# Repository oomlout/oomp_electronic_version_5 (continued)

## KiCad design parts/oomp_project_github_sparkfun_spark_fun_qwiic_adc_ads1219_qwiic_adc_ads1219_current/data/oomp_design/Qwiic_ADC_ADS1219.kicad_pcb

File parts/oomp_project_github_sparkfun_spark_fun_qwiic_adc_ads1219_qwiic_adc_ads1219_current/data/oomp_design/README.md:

# OOMP KiCad design copy

Open `Qwiic_ADC_ADS1219.kicad_pro` (or the `.kicad_pcb` / `.kicad_sch`) in KiCad. Local OOMP libraries are under `libraries/`. Original inputs are preserved in [../original/](../original/).

Only verified unchanged installed KiCad defaults were renamed. Modified, custom, unmatched and unavailable items remain unchanged. Soldering variants are never swapped during conversion. Existing pad coordinates, nets and UUIDs are preserved.

See [conversion_report.yaml](conversion_report.yaml) for every conversion and skip. Copy this directory before editing; regeneration refuses to overwrite edited design files.

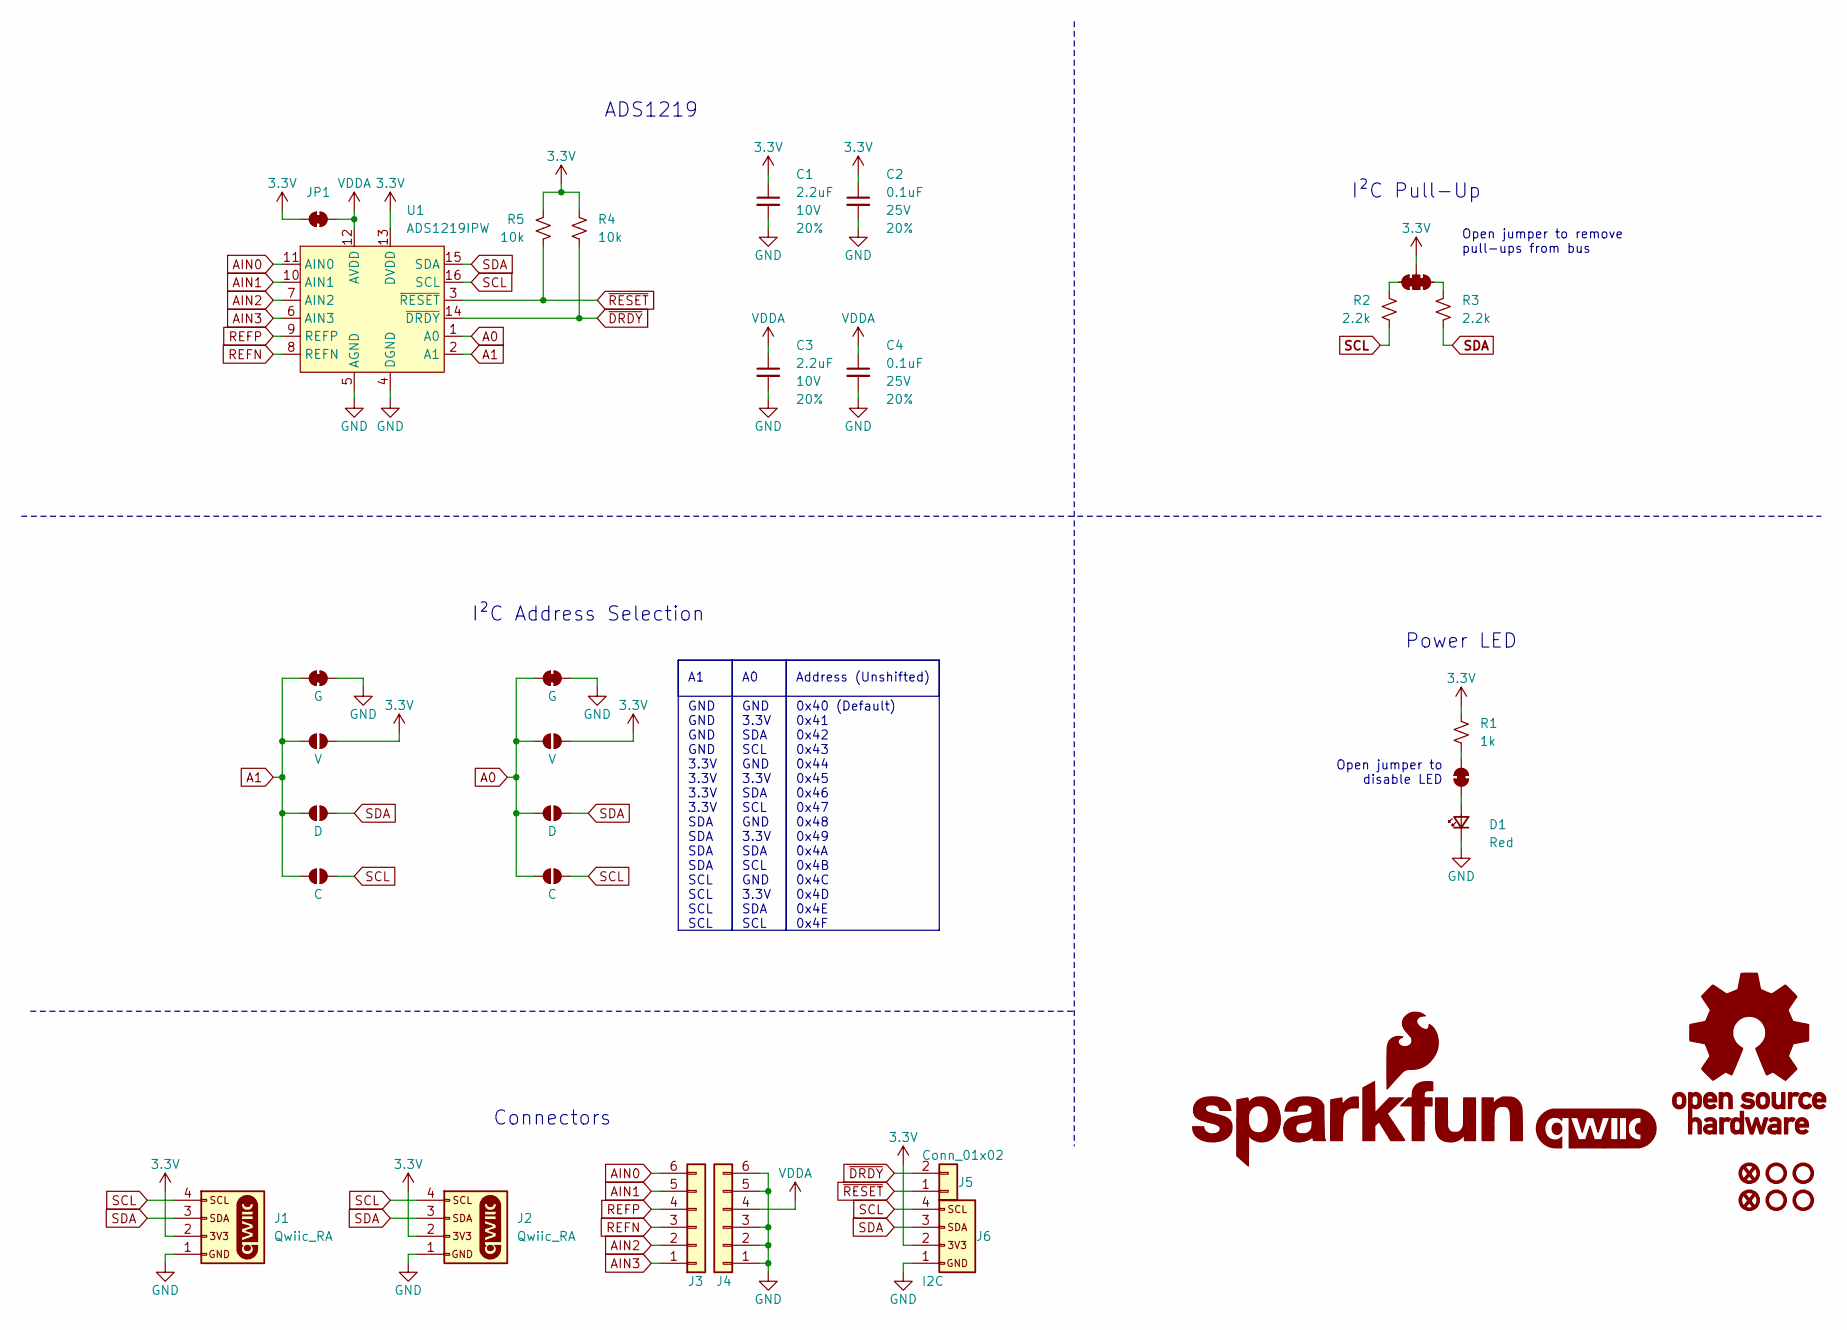
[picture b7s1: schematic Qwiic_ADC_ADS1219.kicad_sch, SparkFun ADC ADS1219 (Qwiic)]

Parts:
C1, C3: 2.2uF; C_0603_1608Metric; Voltage 10V; Tolerance 20%
C2, C4: 0.1uF; C_0603_1608Metric; Voltage 25V; Tolerance 20%
D1: Red; LED_0603_1608Metric_Red
FID1, FID3: Fiducial_0.5mm; Fiducial_0.5mm_Mask1mm
G1: SparkFun_Logo
J1, J2: Qwiic_RA; JST_SMD_1.0mm-4_Black
J3, J4: Conn_01x06; 1x06
J5: Conn_01x02; 1x02
J6: I2C; 1x04
JP1, JP2: Jumper_2_NC_Trace
JP3: Jumper_3_NC-2_Trace
JP4, JP8: G; Jumper_2_NC_Trace
JP5, JP9: V; Jumper_2_NO
JP6, JP10: D; Jumper_2_NO
JP7, JP11: C; Jumper_2_NO
R1: 1k; R_0603_1608Metric
R2, R3: 2.2k; R_0603_1608Metric
R4, R5: 10k; R_0603_1608Metric
ST1, ST2, ST3, ST4: Standoff
U1: ADS1219IPW; TSSOP-16

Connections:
3.3V: C1.1, C2.1, J1.2, J2.2, J6.2, JP1.1 (A), JP3.2 (B), JP5.2 (B), JP9.2 (B), R1.2, R4.2, R5.1, U1.13 (DVDD)
A0: JP4.1 (A), JP5.1 (A), JP6.1 (A), JP7.1 (A), U1.1 (A0)
A1: JP8.1 (A), JP9.1 (A), JP10.1 (A), JP11.1 (A), U1.2 (A1)
AIN0: J3.6, U1.11 (AIN0)
AIN1: J3.5, U1.10 (AIN1)
AIN2: J3.2, U1.7 (AIN2)
AIN3: J3.1, U1.6 (AIN3)
GND: C1.2, C2.2, C3.2, C4.2, D1.1 (K), J1.1, J2.1, J4.1, J4.2, J4.3, J4.5, J4.6, J6.1, JP4.2 (B), JP8.2 (B), U1.4 (DGND), U1.5 (AGND)
unnamed: D1.2 (A), JP2.1 (A)
unnamed: JP2.2 (B), R1.1
unnamed: JP3.1 (A), R3.1
unnamed: JP3.3 (C), R2.2
REFN: J3.3, U1.8 (REFN)
REFP: J3.4, U1.9 (REFP)
SCL: J1.4, J2.4, J6.4, JP7.2 (B), JP11.2 (B), R2.1, U1.16 (SCL)
SDA: J1.3, J2.3, J6.3, JP6.2 (B), JP10.2 (B), R3.2, U1.15 (SDA)
VDDA: C3.1, C4.1, J4.4, JP1.2 (B), U1.12 (AVDD)
~DRDY: J5.2, R4.1, U1.14 (~DRDY)
~RESET: J5.1, R5.2, U1.3 (~RESET)

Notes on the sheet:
Open jumper to remove pull-ups from bus
Connectors
Power LED
I²C Address Selection
Open jumper to disable LED
A1 GND GND GND GND 3.3V 3.3V 3.3V 3.3V SDA SDA SDA SDA SCL SCL SCL SCL
Address (Unshifted) 0x40 (Default) 0x41 0x42 0x43 0x44 0x45 0x46 0x47 0x48 0x49 0x4A 0x4B 0x4C 0x4D 0x4E 0x4F
ADS1219
I²C Pull-Up
A0 GND 3.3V SDA SCL GND 3.3V SDA SCL GND 3.3V SDA SCL GND 3.3V SDA SCL

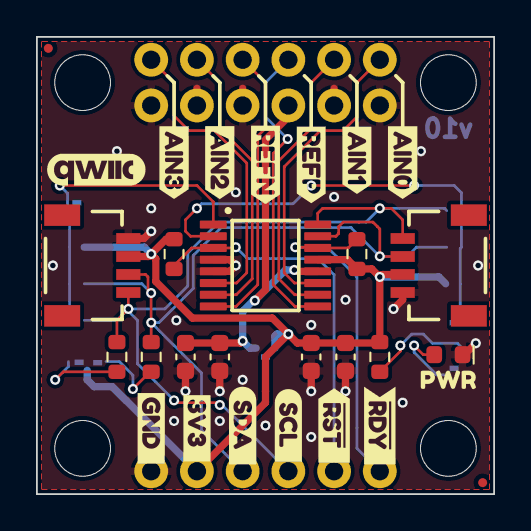
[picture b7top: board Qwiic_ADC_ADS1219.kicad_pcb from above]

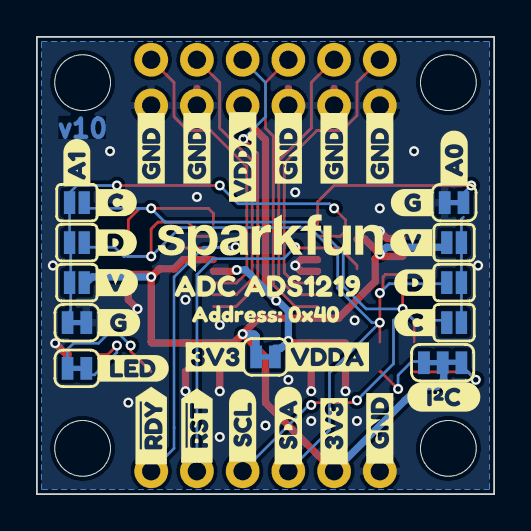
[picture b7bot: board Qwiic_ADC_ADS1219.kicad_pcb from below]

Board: 2 copper layers, 25.4 x 25.4 mm, 75 parts (39 on the bottom side), 19 nets.

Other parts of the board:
kibuzzard-64C3B30F: G***; kibuzzard-64C3B30F
kibuzzard-64C3BD7A: G***; kibuzzard-64C3BD7A
kibuzzard-64C36D1A: G***; kibuzzard-64C36D1A
kibuzzard-64C36D2D: G***; kibuzzard-64C36D2D
kibuzzard-64C36D5B: G***; kibuzzard-64C36D5B
kibuzzard-64C36D6C: G***; kibuzzard-64C36D6C
kibuzzard-64C36D47: G***; kibuzzard-64C36D47
kibuzzard-64C36D91: G***; kibuzzard-64C36D91
kibuzzard-64C37A88: G***; kibuzzard-64C37A88
kibuzzard-64C37CC9: G***; kibuzzard-64C37CC9
kibuzzard-64C38090: G***; kibuzzard-64C38090
kibuzzard-67BCC03F: G***; kibuzzard-67BCC03F
kibuzzard-67BCE7E0: G***; kibuzzard-67BCE7E0
kibuzzard-67BCE9A5: G***; kibuzzard-67BCE9A5
kibuzzard-67BCE9C9: G***; kibuzzard-67BCE9C9
kibuzzard-67BCE9CD: G***; kibuzzard-67BCE9CD
kibuzzard-67BCE9E1: G***; kibuzzard-67BCE9E1
kibuzzard-67BCE80E: G***; kibuzzard-67BCE80E
kibuzzard-67BCE89D: G***; kibuzzard-67BCE89D
kibuzzard-67BCE805: G***; kibuzzard-67BCE805
kibuzzard-67BCE809: G***; kibuzzard-67BCE809
kibuzzard-67BCE889: G***; kibuzzard-67BCE889
kibuzzard-67BCE896: G***; kibuzzard-67BCE896
kibuzzard-67BCE899: G***; kibuzzard-67BCE899
kibuzzard-67BCEA1E: G***; kibuzzard-67BCEA1E
kibuzzard-67BCEA3A: G***; kibuzzard-67BCEA3A
kibuzzard-67BCEA31: G***; kibuzzard-67BCEA31
kibuzzard-67BCEA48: G***; kibuzzard-67BCEA48
kibuzzard-67BCEA55: G***; kibuzzard-67BCEA55
kibuzzard-67BCEA65: G***; kibuzzard-67BCEA65
kibuzzard-67BCEA70: G***; kibuzzard-67BCEA70
kibuzzard-67BCEAAB: G***; kibuzzard-67BCEAAB
kibuzzard-67BCEAC6, kibuzzard-67BCEAC6#2, kibuzzard-67BCEAC6#3, kibuzzard-67BCEAC6#4, kibuzzard-67BCEAC6#5: G***; kibuzzard-67BCEAC6
kibuzzard-67BCEAE1: G***; kibuzzard-67BCEAE1
kibuzzard-67BCEB1D: G***; kibuzzard-67BCEB1D
kibuzzard-67BCEB15: G***; kibuzzard-67BCEB15
kibuzzard-67BCEB32: G***; kibuzzard-67BCEB32

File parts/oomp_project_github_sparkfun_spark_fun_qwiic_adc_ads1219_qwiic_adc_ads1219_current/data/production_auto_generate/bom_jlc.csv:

Comment,Designator,Footprint,LCSC Part #
0.1uF,"C2,C4",SparkFun-Capacitor:C_0603_1608Metric,C14663
10k,"R4,R5",SparkFun-Resistor:R_0603_1608Metric,C98220
1k,R1,SparkFun-Resistor:R_0603_1608Metric,C2907002
2.2k,"R2,R3",SparkFun-Resistor:R_0603_1608Metric,C4190
2.2uF,"C1,C3",SparkFun-Capacitor:C_0603_1608Metric,C23630
ADS1219IPW,U1,SparkFun-Semiconductor-Standard:TSSOP-16,
C,"JP7,JP11",SparkFun-Jumper:Jumper_2_NO,
Conn_01x02,J5,SparkFun-Connector:1x02,C492401
Conn_01x06,"J3,J4",SparkFun-Connector:1x06,C37208
D,"JP6,JP10",SparkFun-Jumper:Jumper_2_NO,
G,"JP4,JP8",SparkFun-Jumper:Jumper_2_NC_Trace,
I2C,J6,SparkFun-Connector:1x04,C42431795
Qwiic_RA,"J1,J2",SparkFun-Connector:JST_SMD_1.0mm-4_Black,C160404
Red,D1,SparkFun-LED:LED_0603_1608Metric_Red,
V,"JP5,JP9",SparkFun-Jumper:Jumper_2_NO,
~,"JP1,JP2",SparkFun-Jumper:Jumper_2_NC_Trace,
~,JP3,SparkFun-Jumper:Jumper_3_NC-2_Trace,
